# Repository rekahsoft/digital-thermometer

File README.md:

# Simple Digital Thermometer (using [AVR-lcdLib][])

A simple digital thermometer with character LCD display, intended as an example project showing
how to use [AVR-lcdLib][].

Note however, that this project is not yet complete, namely the pcb is not yet completed. See
[Issues](#issues) and/or [Roadmap](#road-map) for more details.

* [Features](#features)
* [Tools](#tools)
* [License](#license)
* [Building](#building)
  * [Hardware](#hardware)
  * [Software](#software)
* [Issues](#issues)
* [Road Map](#road-map)

## Features 

- Uses a LCD character display to show the current temperature in Celsius or Fahrenheit using [AVR-lcdLib][]
- Uses TMP36 temperature sensor to provide +-2 degrees Celsius accuracy
- Has single toggle button to switch between Celsius and Fahrenheit (not yet implemented in firmware)

## Tools 

This project wouldn't be possible without the following great open source tools:

- AVR-GCC, [AVR-libc][], and AVR-binutils which form the compiler toolchain that makes open
  source development for AVR microcontrollers possible.
- [avrdude][] to do in system programming of the AVR microcontrollers
- [Gnu Emacs][], because how else would I enter text?

## License 

Code licensed under ([GPLv3][]. Please see the LICENSE file for full details.

## Building 

### Hardware 

Currently, as mentioned above and in [Issues](#issues), the PCB is not yet developed, though a
circuit diagram is provided. It can be opened with kicad and is located within the
'DigitalThermometer' folder.

### Software <a name="software)</a>

## Issues 

Currently, the pcb has not been completed, but the hardware design has been built on a
breadboard and tested with the current code, which found both to be functioning.

Additionally, the firmware does not currently support having a button to toggle between
displaying the temperature in Celsius or in Fahrenheit.

## Road Map 

- Design a PCB
- Add support for Celsius/Fahrenheit toggle button in firmware

[AVR-lcdLib]: http://git.rekahsoft.ca/AVR-lcdLib
[AVR-libc]: http://www.nongnu.org/avr-libc/
[avrdude]: http://savannah.nongnu.org/projects/avrdude
[Gnu Emacs]: http://www.gnu.org/software/emacs/
[GPLv3]: https://www.gnu.org/licenses/gpl.html

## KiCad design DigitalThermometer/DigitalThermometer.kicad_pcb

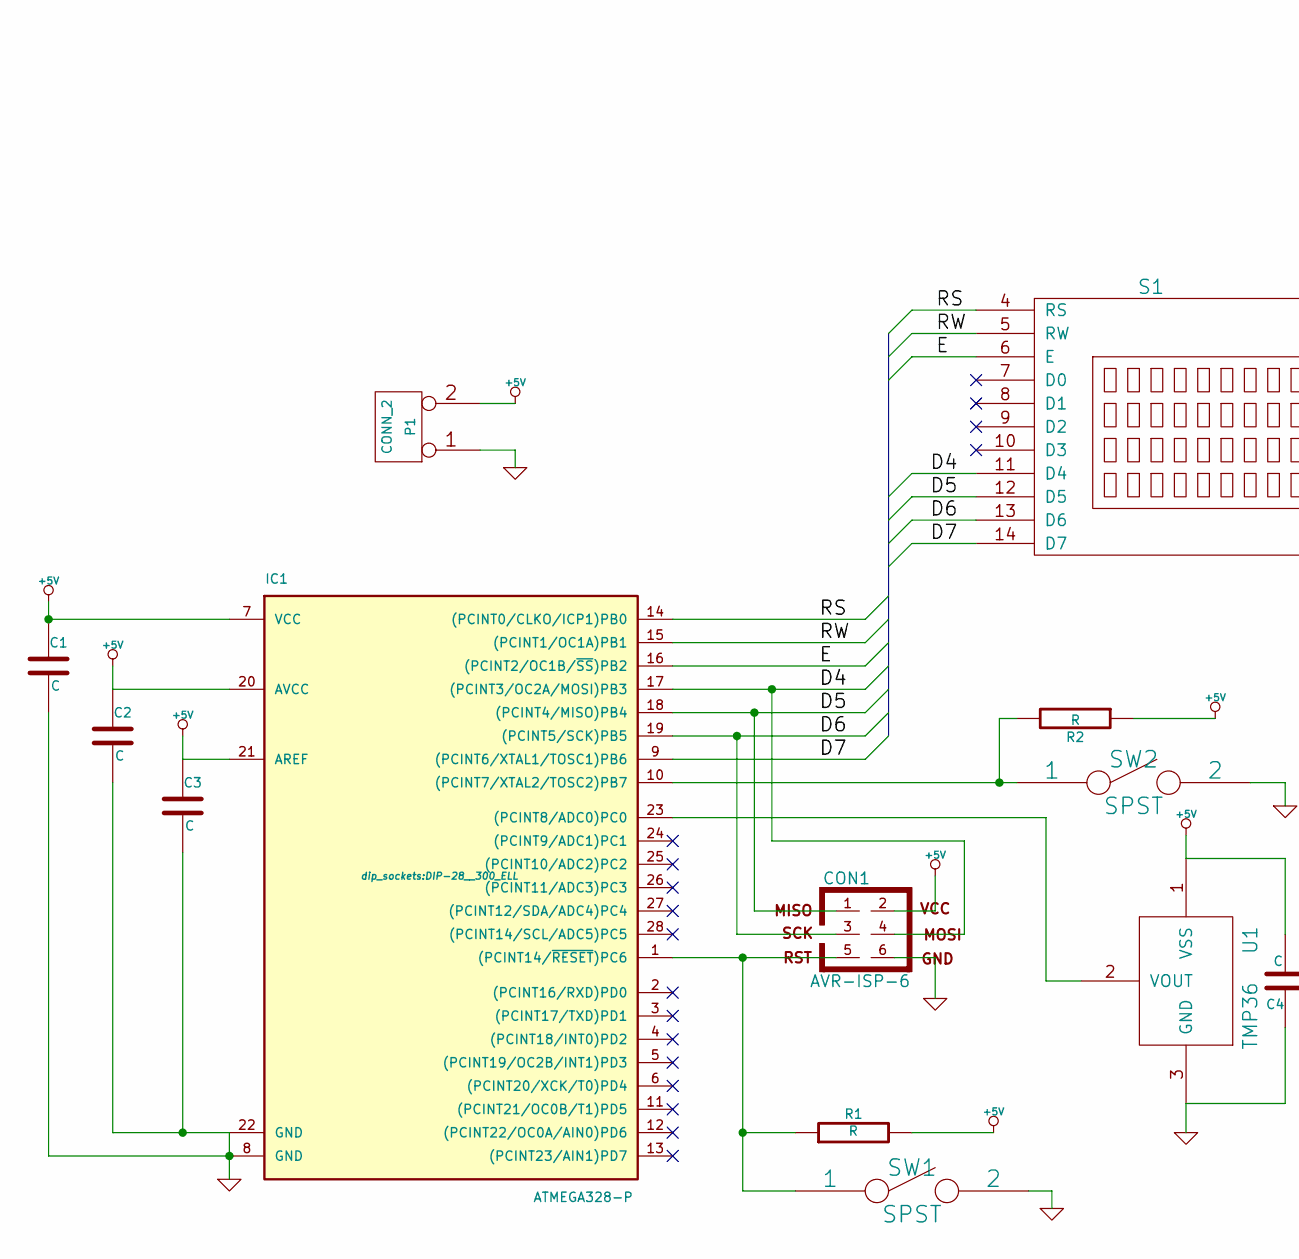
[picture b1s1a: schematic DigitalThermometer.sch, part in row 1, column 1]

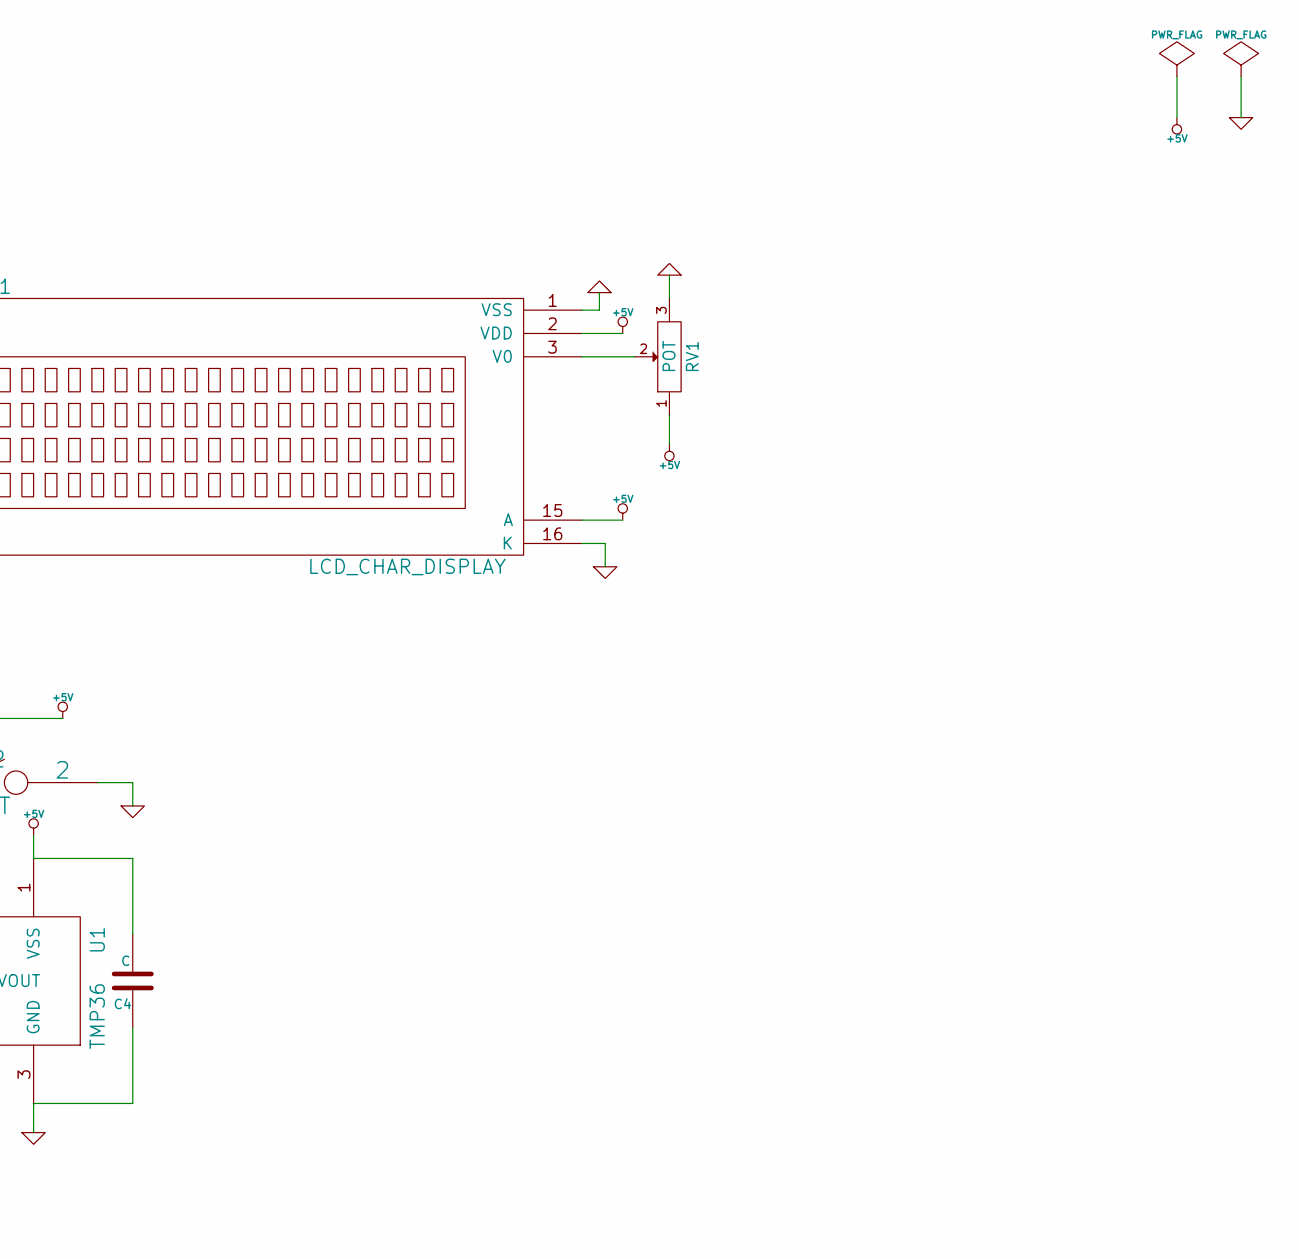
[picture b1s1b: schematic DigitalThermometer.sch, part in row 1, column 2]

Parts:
C1, C2, C3, C4: C; cnp_7x2mm
CON1: AVR-ISP-6; pin_array_3x2
IC1: ATMEGA328-P; DIP-28__300_ELL
P1: CONN_2; PIN_ARRAY_2X1
R1, R2: R; R5
RV1: POT; POACAH
S1: LCD_CHAR_DISPLAY; pin_array_16
SW1, SW2: SPST; SW_PUSH_SMALL
U1: TMP36; TO92

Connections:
+5V: C1.1, C2.1, C3.1, C4.2, CON1.2, IC1.7 (VCC), IC1.20 (AVCC), IC1.21 (AREF), P1.2 (PM), R1.2, R2.1, RV1.1, S1.2 (VDD), S1.15 (A), U1.1 (VSS)
/D4: CON1.4, IC1.17 ((PCINT3/OC2A/MOSI)PB3), S1.11 (D4)
/D5: CON1.1, IC1.18 ((PCINT4/MISO)PB4), S1.12 (D5)
/D6: CON1.3, IC1.19 ((PCINT5/SCK)PB5), S1.13 (D6)
/D7: IC1.9 ((PCINT6/XTAL1/TOSC1)PB6), S1.14 (D7)
/E: IC1.16 ((PCINT2/OC1B/~SS~)PB2), S1.6 (E)
/RS: IC1.14 ((PCINT0/CLKO/ICP1)PB0), S1.4 (RS)
/RW: IC1.15 ((PCINT1/OC1A)PB1), S1.5 (RW)
GND: C1.2, C2.2, C3.2, C4.1, CON1.6, IC1.8 (GND), IC1.22 (GND), P1.1, RV1.3, S1.1 (VSS), S1.16 (K), SW1.2, SW2.2, U1.3 (GND)
unnamed: CON1.5, IC1.1 ((PCINT14/~RESET~)PC6), R1.1, SW1.1
unnamed: IC1.10 ((PCINT7/XTAL2/TOSC2)PB7), R2.2, SW2.1
unnamed: IC1.23 ((PCINT8/ADC0)PC0), U1.2 (VOUT)
unnamed: RV1.2, S1.3 (V0)

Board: 2 copper layers, 14 parts (2 on the bottom side), 13 nets, no tracks yet.

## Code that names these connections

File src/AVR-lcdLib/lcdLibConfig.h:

/**
 * (C) Copyright Collin J. Doering 2015
 *
 * This program is free software: you can redistribute it and/or modify
 * it under the terms of the GNU General Public License as published by
 * the Free Software Foundation, either version 3 of the License, or
 * (at your option) any later version.
 * 
 * This program is distributed in the hope that it will be useful,
 * but WITHOUT ANY WARRANTY; without even the implied warranty of
 * MERCHANTABILITY or FITNESS FOR A PARTICULAR PURPOSE.  See the
 * GNU General Public License for more details.
 * 
 * You should have received a copy of the GNU General Public License
 * along with this program.  If not, see <http://www.gnu.org/licenses/>.
*/

/**
 * @file lcdLibConfig.h
 * @author Collin J. Doering <collin.doering@rekahsoft.ca>
 * @date Oct 4, 2015
 * @brief Configuration file for lcdLib.h
 */

// Includes -------------------------------------------------------------------------------

#include <avr/io.h>

//------------------------------------------------------------------------------------------

/**
  Usage
  =====

  Operates in 3 mutually exclusive modes:
  1. Default Mode
     8-bit mode that requires all its data bus lines be on the same PORT.
  2. EIGHT_BIT_ARBITRARY_PIN_MODE
     8-bit mode that allows the data bus lines to use any IO pin.
  3. FOUR_BIT_MODE
     4-bit mode that allows the data bus lines to use any IO pin.
*/

/*
  Screen characteristics
*/

#define LCD_CHARACTERS_PER_LINE 20      ///< Number of characters per line of the LCD
#define LCD_NUMBER_OF_LINES     4       ///< Number of lines of the LCD
#define LCD_LINE_BEGINNINGS     0x00, \
                                0x40, \
                                0x14, \
                                0x54    ///< Memory locations for each physical line ordered 1 to LCD_NUMBER_OF_LINES

/* Which font to use (can only leave one uncommented) */
#define LCD_FONT_5x8
//#define LCD_FONT_5x10

/* Support ANSI escapes; comment to disable */
//#define LCD_ANSI_ESCAPE_ENABLE

/* Modes */

// Default mode: 8-bit data bus

// 8-bit mode with data bus on arbitrary pins
//#define EIGHT_BIT_ARBITRARY_PIN_MODE

// LCD in 4-bit mode (on arbitrary pins)
#define FOUR_BIT_MODE

/* All mode options */

#define LCD_RS          PB0
#define LCD_RS_PORT     PORTB
#define LCD_RS_DDR      DDRB

#define LCD_RW          PB1
#define LCD_RW_PORT     PORTB
#define LCD_RW_DDR      DDRB

#define LCD_ENABLE      PB2
#define LCD_ENABLE_PORT PORTB
#define LCD_ENABLE_DDR  DDRB

/*
  Mode specific settings
*/

/* Default Mode */

// LCD data bus PORT, PIN and DDR.
#define LCD_DBUS_PORT   PORTB

#define LCD_DBUS_DDR    DDRB
#define LCD_DBUS_PIN    PINB

// This must be set in default mode to the MSB of the data lines
#define LCD_BF          PB7

/* EIGHT_BIT_ARBITRARY_PIN_MODE specific settings */

#define LCD_DBUS0      PB0
#define LCD_DBUS0_PORT PORTB
#define LCD_DBUS0_DDR  DDRB
#define LCD_DBUS0_PIN  PINB

#define LCD_DBUS1      PB1
#define LCD_DBUS1_PORT PORTB
#define LCD_DBUS1_DDR  DDRB
#define LCD_DBUS1_PIN  PINB

#define LCD_DBUS2      PB2
#define LCD_DBUS2_PORT PORTB
#define LCD_DBUS2_DDR  DDRB
#define LCD_DBUS2_PIN  PINB

#define LCD_DBUS3      PB3
#define LCD_DBUS3_PORT PORTB
#define LCD_DBUS3_DDR  DDRB
#define LCD_DBUS3_PIN  PINB

/* FOUR_BIT_MODE and EIGHT_BIT_ARBITRARY_PIN_MODE shared settings */

#define LCD_DBUS4      PB3
#define LCD_DBUS4_PORT PORTB
#define LCD_DBUS4_DDR  DDRB
#define LCD_DBUS4_PIN  PINB

#define LCD_DBUS5      PB4
#define LCD_DBUS5_PORT PORTB
#define LCD_DBUS5_DDR  DDRB
#define LCD_DBUS5_PIN  PINB

#define LCD_DBUS6      PB5
#define LCD_DBUS6_PORT PORTB
#define LCD_DBUS6_DDR  DDRB
#define LCD_DBUS6_PIN  PINB

#define LCD_DBUS7      PB6
#define LCD_DBUS7_PORT PORTB
#define LCD_DBUS7_DDR  DDRB
#define LCD_DBUS7_PIN  PINB


/* LCD delays (in microseconds when unspecified) */

#define LCD_ENABLE_HIGH_DELAY   25
#define LCD_ENABLE_LOW_DELAY    25
#define LCD_INIT_DELAY0         15000
#define LCD_INIT_DELAY1         8200
#define LCD_INIT_DELAY2         200

#define LCD_CLEAR_DISPLAY_DELAY 16000
#define LCD_RETURN_HOME_DELAY   16000
#define LCD_GENERIC_INSTR_DELAY 50

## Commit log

2016-01-17 Initial commit, splitting example from AVR-lcdLib
2016-01-17 Remove AVR-lcdLib before adding its subtree
2016-01-17 Squashed 'src/AVR-lcdLib/' content from commit 3a38d3f
    git-subtree-dir: src/AVR-lcdLib
    git-subtree-split: 3a38d3ff18b7acf972617940ebcc0ec45e659c49
2016-01-17 Make project specific changes to lcdLibConfig.h
    Make changes to the configuration header provided bu AVR-lcdLib to
    achieve the following:
    * Configure pin assignments to match the kicad schematic provided in the
    DigitalThermometer directory
    * Use 4-bit mode
    * Turn off ANSI escapes
